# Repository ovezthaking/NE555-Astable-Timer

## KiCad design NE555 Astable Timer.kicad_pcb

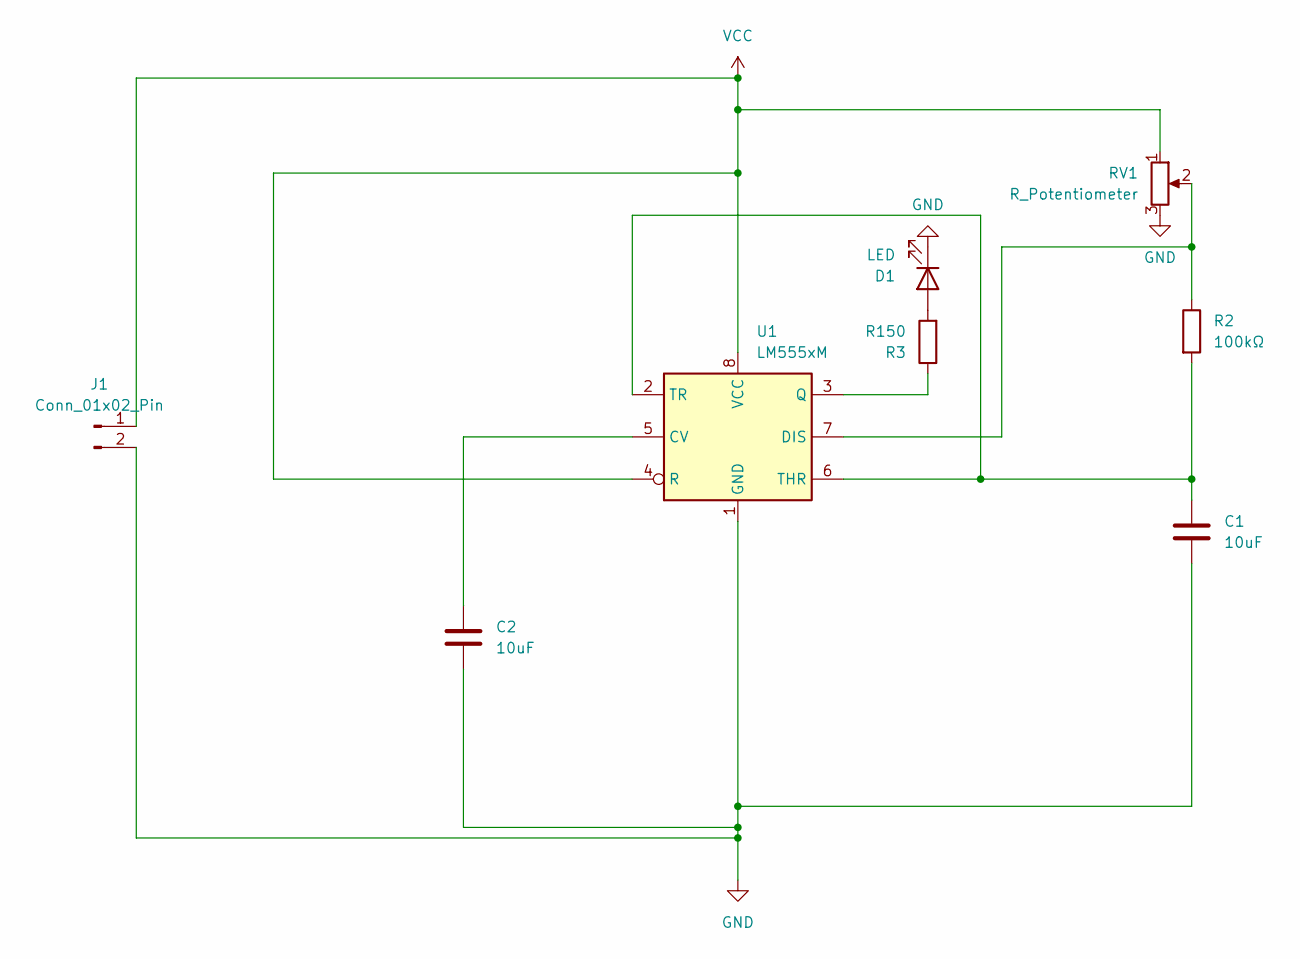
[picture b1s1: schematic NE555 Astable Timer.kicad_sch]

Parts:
C1, C2: 10uF; CP_Radial_Tantal_D5.0mm_P5.00mm
D1: LED; LED_D3.0mm
J1: Conn_01x02_Pin; PinHeader_1x02_P2.00mm_Vertical
R2: 100kΩ; R_Axial_DIN0207_L6.3mm_D2.5mm_P7.62mm_Horizontal
R3: R150; R_0805_2012Metric_Pad1.20x1.40mm_HandSolder
RV1: R_Potentiometer; Potentiometer_ACP_CA9-H3,8_Horizontal
U1: LM555xM; SOIC-8_3.9x4.9mm_P1.27mm

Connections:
GND: C1.2, C2.2, D1.1 (K), J1.2, RV1.3, U1.1 (GND)
unnamed: D1.2 (A), R3.2
unnamed: C2.1, U1.5 (CV)
unnamed: R2.1, RV1.2, U1.7 (DIS)
unnamed: R3.1, U1.3 (Q)
unnamed: C1.1, R2.2, U1.2 (TR), U1.6 (THR)
VCC: J1.1, RV1.1, U1.4 (R), U1.8 (VCC)

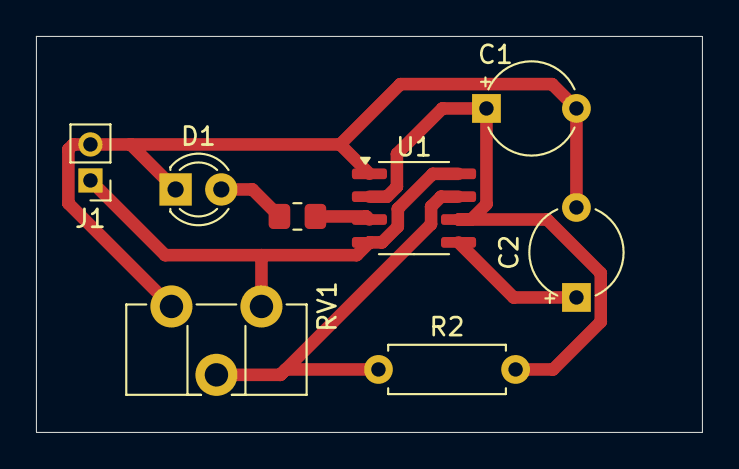
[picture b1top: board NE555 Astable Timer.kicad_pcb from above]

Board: 2 copper layers, 37.0 x 22.0 mm, 8 parts (0 on the bottom side), 7 nets.

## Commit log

2025-04-16 PCB and schema NE555 Astable timer
2025-04-16 potentiometer update
2025-04-17 update and values
